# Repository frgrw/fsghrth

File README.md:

# Design Files for Wired Sculpt Conversion Board

This repository contains the schematic and layout files for the [Microsoft Sculpt Wired Conversion Mod](https://chadaustin.me/2021/02/wired-sculpt/).

To get the board manufactured:
1) Install Kicad & the PCBWay plugin. Use the plugin to start an order, select HASL lead-free if you want lead-free. The other defaults should be fine. Check the box for Assembly service
2) Upload the BOM (bill of materials) and component placement file. These are generated from Kicad: use Tools > "Generate BOM" from the Schematic Editor, and File > "Fabrication Outputs" > "Component placement (.pos)" from the PCB Editor.

## Project Updates

### 2023-02-20

rev6 board with USB-C

Also has some adjustments to board layout, and removes RST switch header to reduce BOM

### 2023-01-06

rev5 board with minor updates.

Rearrange the board layout to fix some Design Rule Check failures and extend the board to match the full layout of the original PCB. A few parts were replaced too, due to supply shortages. No functional changes were made.

### 2021-09-07

The rev4 board design is complete.

When I upgraded the 30-pin ribbon connector to one that fit better, it lowered the resistance to the LEDs. This caused me to burn the microcontroller on a test rev3 board by drawing too much current. So the question became: what values are appropriate for "maximum" brightness on both red and green. Today I found that, given a 5.15V VUSB, whatever resistance in the flex cable, and whatever voltage drop on the LEDs, 150 Ohms gives an even brightness on both red and green. Green draws about 15 mA and red about 10 mA, both within USB low-power spec and the current limits on the microcontroller.

I added an [outputs](outputs/) directory containing the different revisions, and gerber files and drill files generated for either PCBWay or OSH Park.

The biggest challenge right now is the chip shortage. Even some of the capacitors I chose are out of stock. The hardest component to acquire is the ESD protection IC: USBLC6-2SC6. The USBLC6-4SC6 is available, but it would require some tweaking to the PCB layout.

On the software side of things, I added an internal ring buffer for debugging the debouncer. It can be dumped to the HID debug channel by holding both shifts and pressing H. I am trying to figure out why, with my custom low-latency debouncer, sometimes "the" comes out as "theb". For anyone that isn't trying to optimize latency as much as me, you can just run with the default QMK debouncer, which I've never seen produce phantom keys.

### 2021-05-02

One thing that annoyed me about the previous board design was that neither LED was hooked up to a PWM-capable pin and that the green one couldn't be driven, since it wants -5V. I want both lights to work and both to be dimmable.

Rev3 includes a charge pump to produce -5V and two MOSFETs that allow switching the green cathode with PWM.

I also figured out how the Fn switch works: it's a resistor divider that toggles 47K pull-down on a pin with a permanent 1M pull-up. Rev3 includes said 1M pull-up, so the firmware can read the Fn switch's state.

Sadly, it looks like there were many arrangements of media keys on the Sculpt over the years, and most of the media keys have nonsensical icons with behavior that differs on each platform. I'll try to make at least volume and play/pause work.

The parts for board rev 3 arrived last week. Some adjustments were required due to the chip shortage, but it's not too bad. The microcontroller is still available at least.

I attempted assembly of one, and it worked fine, but I screwed up the red and green pins, so I cut some traces and bodged in some kynar wire.

Both lights work!

I have not tested PWM. I did observe that twice as much current is being drawn for each light as I expected. I fear 40 mA could burn out the lights, so I plan to measure an appropriate series resistor this week. It's possible I never had this problem before because I was using a worse-fitting ribbon connector previously. In the past, I always measured 100 Ohms on every pin, but never tested the new ribbon connector.

Also, it kind of sucks that the LED brightness is a function of USB voltage (anywhere between 4.6 V and 5.25 V), but I don't want to include a regulator...

Assembly took about five hours for one board. A lot of that was getting my desk set up. I imagine I could do three boards in ... eight? I think if I used a stencil, hot air assembly could go pretty quickly. Especially if I had a preheater like the MHP30.

A couple people have suggested I set up an Etsy, but if I properly priced in hours of my labor, it would get prohibitive. And I don't want to deal with returns and warranties.

Remaining items before I can say the board is done:
* Order a fourth PCB design with fixed green and red pins
* Include an 0603 resistor on each
* Fix the debouncer
* Add a media key QMK layer, enabled with the Fn switch.

### 2021-04-27

In February, I tried pushing latency further than QMK offers out of the box. I switched from the default debouncer to sym_eager_pk, but since then I've observed some false keydowns and occasionally a phantom keypress. It's common for "the" to produce "theb". (Note that I use the Dvorak key layout.) I haven't looked at the matrix, but it's clear some debouncing is needed on keydown.

I'm planning on writing a custom debouncer that requires at least two frames for a keydown to register and at least 10 ms for a keyup. Having never done AVR optimization, I am trying to get a [simavr](https://github.com/buserror/simavr) benchmark harness up to make sure I don't regress the scan rate.

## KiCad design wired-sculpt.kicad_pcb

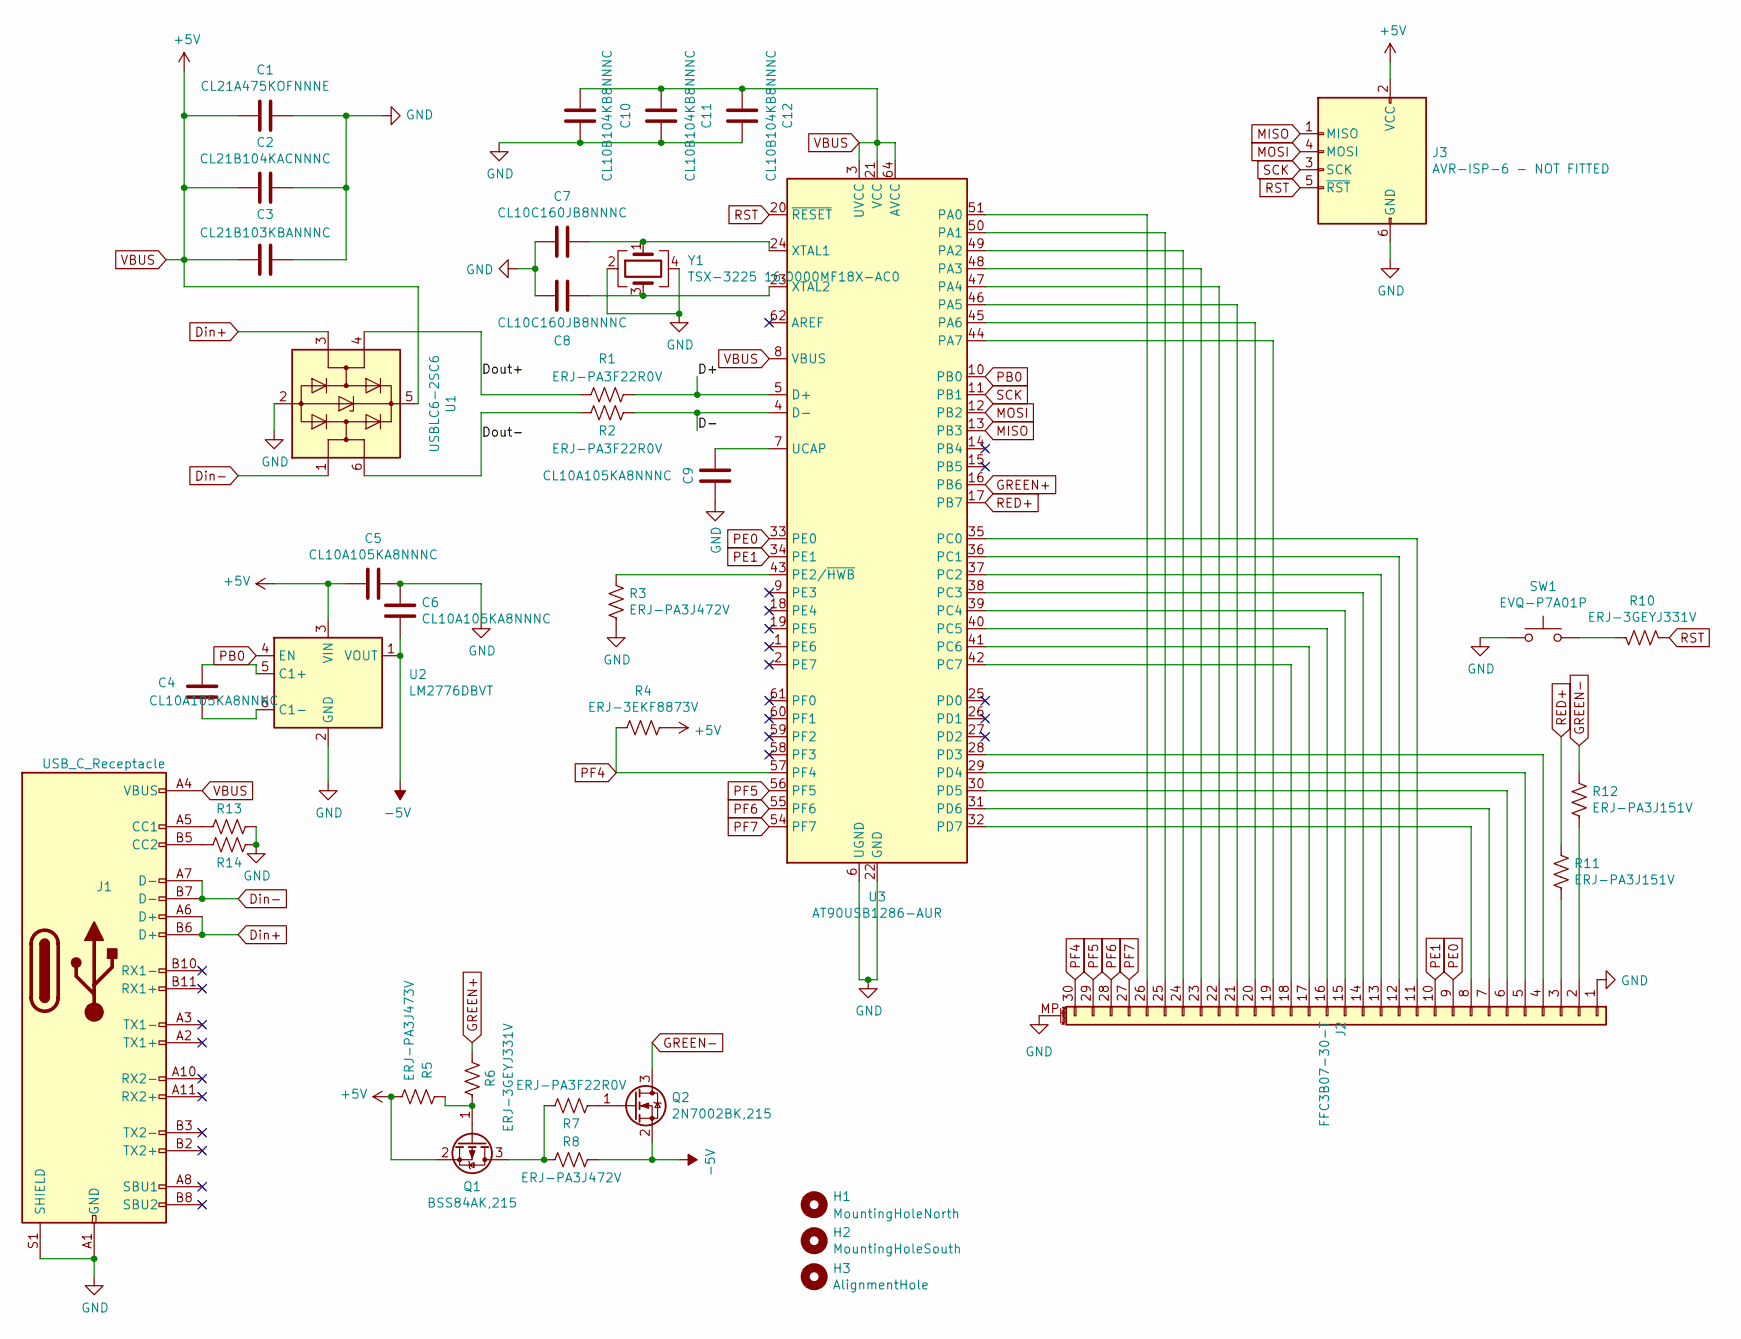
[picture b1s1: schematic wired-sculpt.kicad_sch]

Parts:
C1: CL21A475KOFNNNE; C_0805_2012Metric; MPN CL21A475KOFNNNE
C2: CL21B104KACNNNC; C_0805_2012Metric; MPN CL21B104KACNNNC
C3: CL21B103KBANNNC; C_0805_2012Metric; MPN CL21B103KBANNNC
C4, C5, C6, C9: CL10A105KA8NNNC; C_0603_1608Metric; MPN CL10A105KA8NNNC
C7, C8: CL10C160JB8NNNC; C_0603_1608Metric; MPN CL10C160JB8NNNC
C10, C11, C12: CL10B104KB8NNNC; C_0603_1608Metric; MPN CL10B104KB8NNNC
H1: MountingHoleNorth; MountingHole_2.2mm_M2
H2: MountingHoleSouth; MountingHole_2.2mm_M2
H3: AlignmentHole; MountingHole_3mm
J1: USB_C_Receptacle; USB_C_Receptacle_Amphenol_12401610E4-2A; MPN 12401610E4#2A
J2: FFC3B07-30-T; TE_3-84952-0_1x30-1MP_P1.0mm_Horizontal; MPN FFC3B07-30-T
J3: AVR-ISP-6 - NOT FITTED; IDC-Header_2x03_P2.54mm_Vertical; MPN AVR-ISP-6 - NOT FITTED
Q1: BSS84AK,215; SOT-23; MPN BSS84AK,215
Q2: 2N7002BK,215; SOT-23; MPN 2N7002BK,215
R1, R2, R7: ERJ-PA3F22R0V; R_0603_1608Metric; MPN ERJ-PA3F22R0V
R3, R8: ERJ-PA3J472V; R_0603_1608Metric; MPN ERJ-PA3J472V
R4: ERJ-3EKF8873V; R_0603_1608Metric; MPN ERJ-3EKF8873V
R5: ERJ-PA3J473V; R_0603_1608Metric; MPN ERJ-PA3J473V
R6, R10: ERJ-3GEYJ331V; R_0603_1608Metric; MPN ERJ-3GEYJ331V
R11, R12: ERJ-PA3J151V; R_0603_1608Metric; MPN ERJ-PA3J151V
R13, R14: ERJ-3EKF5101V; R_0603_1608Metric; MPN ERJ-3EKF5101V
SW1: EVQ-P7A01P; SW_SPST_EVQP7A; MPN EVQ-P7A01P
U1: USBLC6-2SC6; SOT-23-6; MPN USBLC6-2SC6
U2: LM2776DBVT; SOT-23-6; MPN LM2776DBVT
U3: AT90USB1286-AUR; TQFP-64_14x14mm_P0.8mm; MPN AT90USB1286-AUR
Y1: TSX-3225 16.0000MF18X-AC0; Crystal_SMD_3225-4Pin_3.2x2.5mm; MPN TSX-3225 16.0000MF18X-AC0

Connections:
-5V: C6.2, Q2.2 (S), R8.1, U2.1 (VOUT)
/D+: R1.1, U3.5 (D+)
/D-: R2.1, U3.4 (D-)
/Dout+: R1.2, U1.4 (I/O2)
/Dout-: R2.2, U1.6 (I/O1)
Din+: J1.A6 (D+), J1.B6 (D+), U1.3 (I/O2)
Din-: J1.A7 (D-), J1.B7 (D-), U1.1 (I/O1)
GND: C1.1, C2.1, C3.1, C5.1, C6.1, C7.2, C8.2, C9.2, C10.1, C11.1, C12.1, J1.A1 (GND), J1.A12 (GND), J1.B1 (GND), J1.B12 (GND), J1.S1 (SHIELD), J2.1, J2.MP (MountPin), J3.6 (GND), R3.2, R13.1, R14.1, SW1.1, U1.2 (GND), U2.2 (GND), U3.6 (UGND), U3.22 (GND), U3.53 (GND), U3.63 (GND), Y1.2, Y1.4
GREEN+: R6.2, U3.16 (PB6)
GREEN-: Q2.3 (D), R12.1
MISO: J3.1 (MISO), U3.13 (PB3)
MOSI: J3.4 (MOSI), U3.12 (PB2)
unnamed: C4.1, U2.5 (C1+)
unnamed: C4.2, U2.6 (C1-)
unnamed: C7.1, U3.24 (XTAL1), Y1.1
unnamed: C8.1, U3.23 (XTAL2), Y1.3
unnamed: C9.1, U3.7 (UCAP)
unnamed: J1.A5 (CC1), R13.2
unnamed: J1.B5 (CC2), R14.2
unnamed: J2.2, R12.2
unnamed: J2.3, R11.2
unnamed: J2.4, U3.28 (PD3)
unnamed: J2.5, U3.29 (PD4)
unnamed: J2.6, U3.30 (PD5)
unnamed: J2.7, U3.31 (PD6)
unnamed: J2.8, U3.32 (PD7)
unnamed: J2.11, U3.35 (PC0)
unnamed: J2.12, U3.36 (PC1)
unnamed: J2.13, U3.37 (PC2)
unnamed: J2.14, U3.38 (PC3)
unnamed: J2.15, U3.39 (PC4)
unnamed: J2.16, U3.40 (PC5)
unnamed: J2.17, U3.41 (PC6)
unnamed: J2.18, U3.42 (PC7)
unnamed: J2.19, U3.44 (PA7)
unnamed: J2.20, U3.45 (PA6)
unnamed: J2.21, U3.46 (PA5)
unnamed: J2.22, U3.47 (PA4)
unnamed: J2.23, U3.48 (PA3)
unnamed: J2.24, U3.49 (PA2)
unnamed: J2.25, U3.50 (PA1)
unnamed: J2.26, U3.51 (PA0)
unnamed: Q1.1 (G), R5.1, R6.1
unnamed: Q1.3 (D), R7.2, R8.2
unnamed: Q2.1 (G), R7.1
unnamed: R3.1, U3.43 (PE2/~HWB)
unnamed: R10.2, SW1.2
PB0: U2.4 (EN), U3.10 (PB0)
PE0: J2.9, U3.33 (PE0)
PE1: J2.10, U3.34 (PE1)
PF4: J2.30, R4.2, U3.57 (PF4)
PF5: J2.29, U3.56 (PF5)
PF6: J2.28, U3.55 (PF6)
PF7: J2.27, U3.54 (PF7)
RED+: R11.1, U3.17 (PB7)
RST: J3.5 (~RST), R10.1, U3.20 (~RESET)
SCK: J3.3 (SCK), U3.11 (PB1)
VBUS: C1.2, C2.2, C3.2, C5.2, C10.2, C11.2, C12.2, J1.A4 (VBUS), J1.A9 (VBUS), J1.B4 (VBUS), J1.B9 (VBUS), J3.2 (VCC), Q1.2 (S), R4.1, R5.2, U1.5 (VBUS), U2.3 (VIN), U3.3 (UVCC), U3.8 (VBUS), U3.21 (VCC), U3.52 (VCC), U3.64 (AVCC)

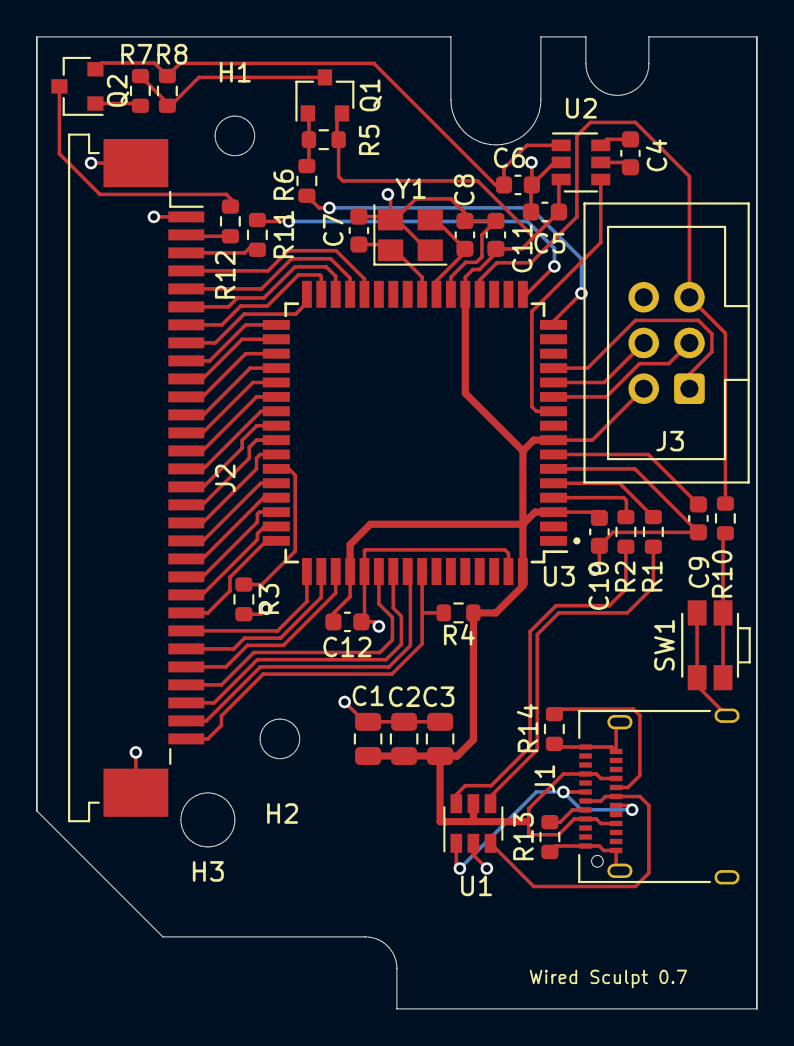
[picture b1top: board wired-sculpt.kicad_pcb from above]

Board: 2 copper layers, 40.0 x 54.0 mm, 38 parts (0 on the bottom side), 58 nets.

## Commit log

2022-12-30 Add .gitignore
2022-12-30 Fix linkage of AT90 symbol
2022-12-30 Extend PCB to fully match original
2022-12-30 Redo layout to resolve some DRC errors
2023-01-07 Fix interior edge cut radius
2023-01-07 Change microcontroller and one FET MPN
    Fixes mismatch that PCBWay flagged
2023-01-07 Copy MPN back to Value field
    This is for compatbility with the JLCPCB plugin
2023-01-07 Add MPN to all components
2023-01-07 Update README with rev5 board
2023-01-07 Properly ground mounting pads for FFC
2023-01-07 Exclude holes and ISP from BOM
2023-02-15 Shift header down 1mm
    This fits more closely to the original board
2023-02-17 Remove reset switch header
2023-02-20 Change connector to USB-C
2023-03-06 Change reset switch to horizontal
2023-03-12 Increase H3 to 3mm
    Slightly more tolerance is needed. Board fit in one of my keyboards, but
    not the other
2023-03-13 Remove on-board status LED
2023-03-13 Bump on-board version number
2023-03-13 Remove exec bit from README.md
2023-03-13 Add manufacturing instructions to readme
2023-03-13 Change output file path for .pos file
